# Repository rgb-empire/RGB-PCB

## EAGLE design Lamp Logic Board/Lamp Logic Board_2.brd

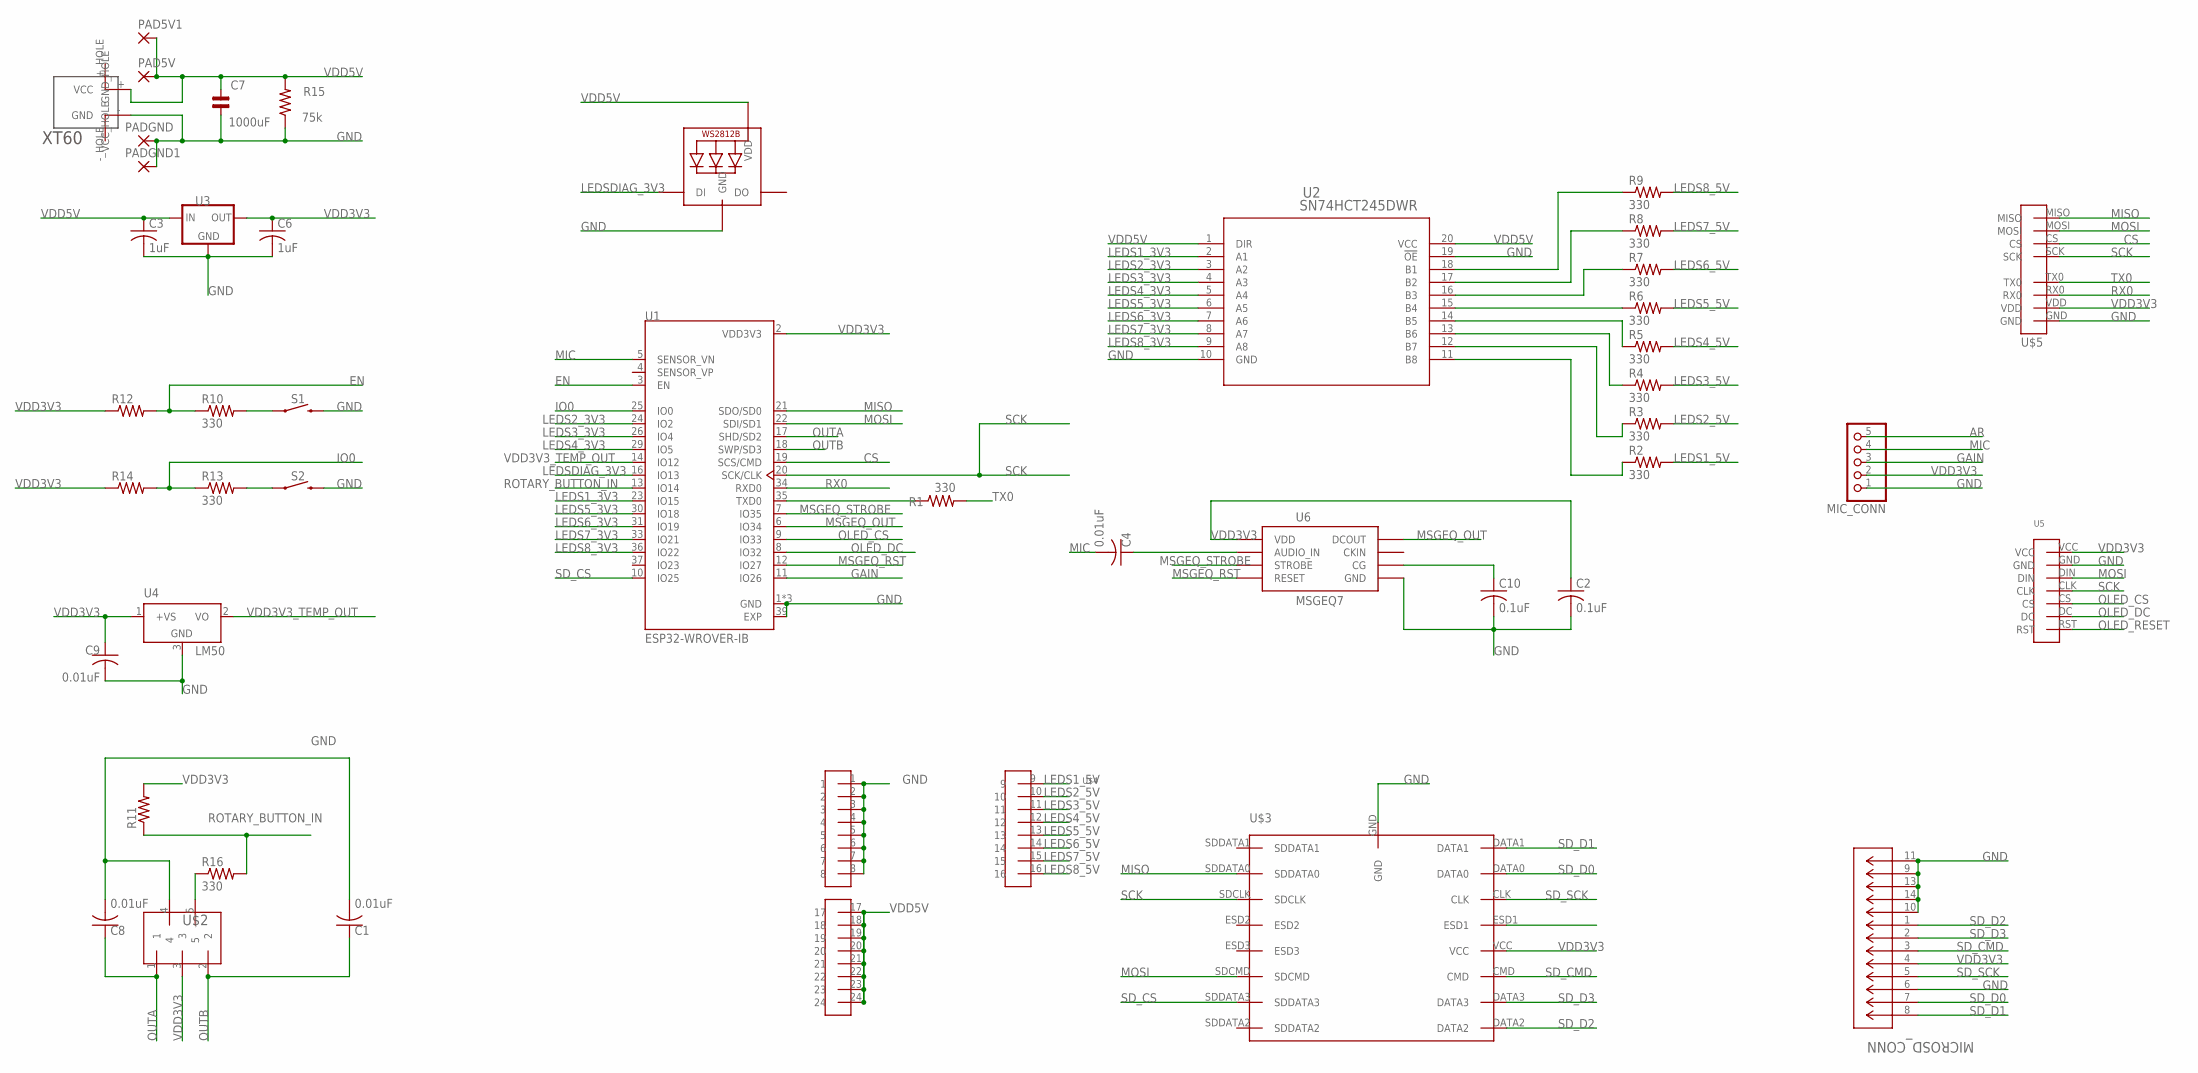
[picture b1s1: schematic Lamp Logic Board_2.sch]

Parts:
C1, C4, C8, C9: 0.01uF; C0402
C2, C10: 0.1uF; C0805
C3, C6: 1uF; C0402
C7: 1000uF; ENP2,0-5
LED1: WS2812B5050; WS2812B
MICROSD_CONN: LLC; CON00218_8
MIC_CONN: PINHD-1X5; 1X05
PAD5V, PAD5V1: SMD5; SMD2,54-5,08
PADGND, PADGND1: SMD5; SMD2,54-5,08
R1, R2, R3, R4, R5, R6, R7, R8, R9, R10, R13, R16: 330; R1206
R11, R12, R14: R-US_R0603; R0603
R15: 75k; 0309/12
S1, S2: MOMENTARY-SWITCH-SPST-SMD-6.0X3.5MM; TACTILE_SWITCH_SMD_6.0X3.5MM
U1: ESP32-WROVER-IB; XCVR_ESP32-WROVER-I
U2: SN74HCT245DWR; DW20
U3: LM1117MP-1.8; SOT223
U4: LM50; SOT23
U5: SPIOLED_STANDOFF; SPIOLED_STADOFF
U6: MSGEQ7DIL; DIL-08
U$1: XT60
U$2: EN11-HSM1AF15; EN11-HSM
U$3: CM1624-08DE
U$4: 3X8PINHEAD
U$5: 2X4PINHEAD

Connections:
AR: MIC_CONN.5
CS: U1.19 (SCS/CMD), U$5.CS
EN: R10.1, R12.2, U1.3 (EN)
GAIN: MIC_CONN.3, U1.11 (IO26)
GND: C1.2, C2.2, C3.2, C6.2, C7.1, C8.2, C9.2, C10.2, LED1.3-GND (GND), MICROSD_CONN.6, MICROSD_CONN.9, MICROSD_CONN.10, MICROSD_CONN.11, MICROSD_CONN.13, MICROSD_CONN.14, MIC_CONN.1, PADGND.1, PADGND1.1, R15.1, S1.2, S2.2, U1.1 (GND), U1.15 (GND), U1.38 (GND), U1.39 (EXP), U2.10 (GND), U2.19 (!OE), U3.1 (GND), U4.3 (GND), U5.GND, U6.2 (GND), U$1.- (GND), U$2.4, U$3.GND, U$4.1, U$4.2, U$4.3, U$4.4, U$4.5, U$4.6, U$4.7, U$4.8, U$5.GND
IO0: R13.1, R14.2, U1.25 (IO0)
LEDS1_3V3: U1.23 (IO15), U2.2 (A1)
LEDS1_5V: R2.2, U$4.9
LEDS2_3V3: U1.24 (IO2), U2.3 (A2)
LEDS2_5V: R3.2, U$4.10
LEDS3_3V3: U1.26 (IO4), U2.4 (A3)
LEDS3_5V: R4.2, U$4.11
LEDS4_3V3: U1.29 (IO5), U2.5 (A4)
LEDS4_5V: R5.2, U$4.12
LEDS5_3V3: U1.30 (IO18), U2.6 (A5)
LEDS5_5V: R6.2, U$4.13
LEDS6_3V3: U1.31 (IO19), U2.7 (A6)
LEDS6_5V: R7.2, U$4.14
LEDS7_3V3: U1.33 (IO21), U2.8 (A7)
LEDS7_5V: R8.2, U$4.15
LEDS8_3V3: U1.36 (IO22), U2.9 (A8)
LEDS8_5V: R9.2, U$4.16
LEDSDIAG_3V3: LED1.4-DIN (DI), U1.16 (IO13)
MIC: C4.2, MIC_CONN.4, U1.5 (SENSOR_VN)
MISO: U1.21 (SDO/SD0), U$3.SDDATA0, U$5.MISO
MOSI: U1.22 (SDI/SD1), U5.DIN, U$3.SDCMD, U$5.MOSI
MSGEQ_OUT: U1.6 (IO34), U6.3 (DCOUT)
MSGEQ_RST: U1.12 (IO27), U6.7 (RESET)
MSGEQ_STROBE: U1.7 (IO35), U6.4 (STROBE)
unnamed: R9.1, U2.18 (B1)
unnamed: R1.1, U1.35 (TXD0)
unnamed: C4.1, U6.5 (AUDIO_IN)
unnamed: C10.1, U6.6 (CG)
unnamed: R16.1, U$2.5
unnamed: R8.1, U2.17 (B2)
unnamed: R13.2, S2.1
unnamed: R10.2, S1.1
unnamed: R7.1, U2.16 (B3)
unnamed: R6.1, U2.15 (B4)
unnamed: R5.1, U2.14 (B5)
unnamed: R4.1, U2.13 (B6)
unnamed: R3.1, U2.12 (B7)
unnamed: R2.1, U2.11 (B8)
OLED_CS: U1.9 (IO33), U5.CS
OLED_DC: U1.8 (IO32), U5.DC
OLED_RESET: U5.RST
OUTA: C8.1, U1.17 (SHD/SD2), U$2.1
OUTB: C1.1, U1.18 (SWP/SD3), U$2.2
ROTARY_BUTTON_IN: R11.1, R16.2, U1.13 (IO14)
RX0: U1.34 (RXD0), U$5.RX0
SCK: U1.20 (SCK/CLK), U5.CLK, U$3.SDCLK, U$5.SCK
SD_CMD: MICROSD_CONN.3, U$3.CMD
SD_CS: U1.10 (IO25), U$3.SDDATA3
SD_D0: MICROSD_CONN.7, U$3.DATA0
SD_D1: MICROSD_CONN.8, U$3.DATA1
SD_D2: MICROSD_CONN.1, U$3.DATA2
SD_D3: MICROSD_CONN.2, U$3.DATA3
SD_SCK: MICROSD_CONN.5, U$3.CLK
TX0: R1.2, U$5.TX0
VDD3V3: C2.1, C6.1, C9.1, MICROSD_CONN.4, MIC_CONN.2, R11.2, R12.1, R14.1, U1.2 (VDD3V3), U3.2 (OUT), U3.4 (OUT), U4.1 (+VS), U5.VCC, U6.1 (VDD), U$2.3, U$3.VCC, U$5.VDD
VDD3V3_TEMP_OUT: U1.14 (IO12), U4.2 (VO)
VDD5V: C3.1, C7.2, LED1.1-VDD (VDD), PAD5V.1, PAD5V1.1, R15.2, U2.1 (DIR), U2.20 (VCC), U3.3 (IN), U$1.+ (VCC), U$4.17, U$4.18, U$4.19, U$4.20, U$4.21, U$4.22, U$4.23, U$4.24

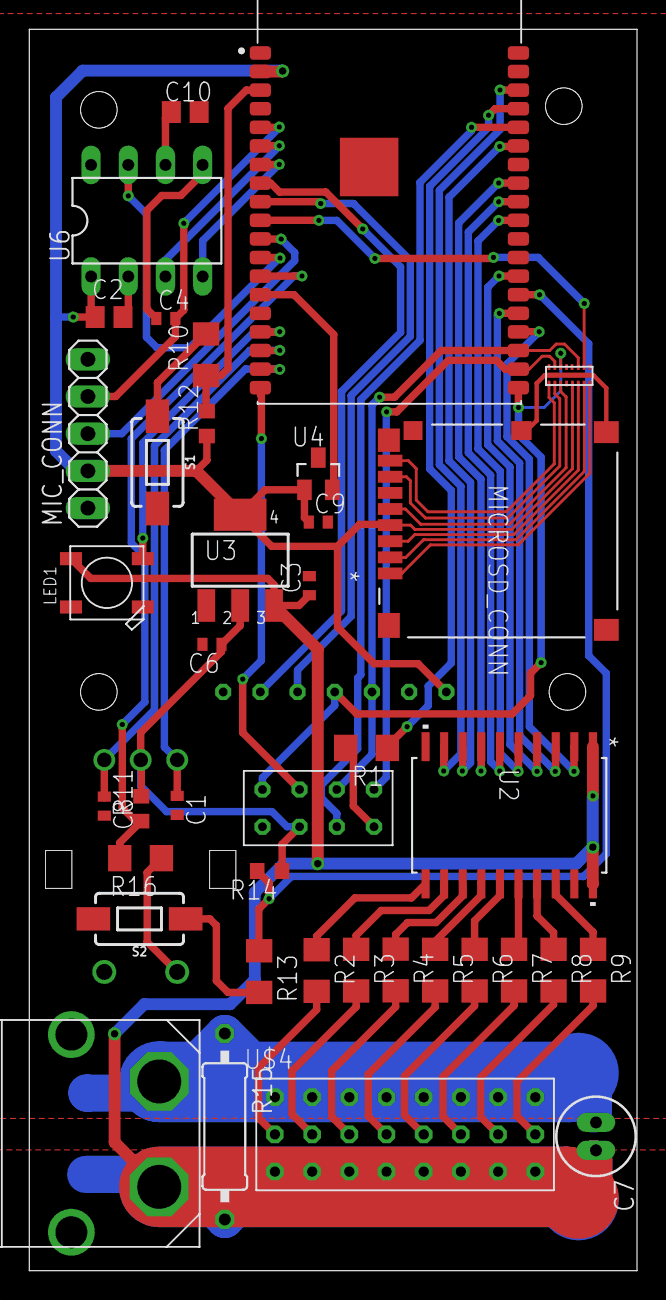
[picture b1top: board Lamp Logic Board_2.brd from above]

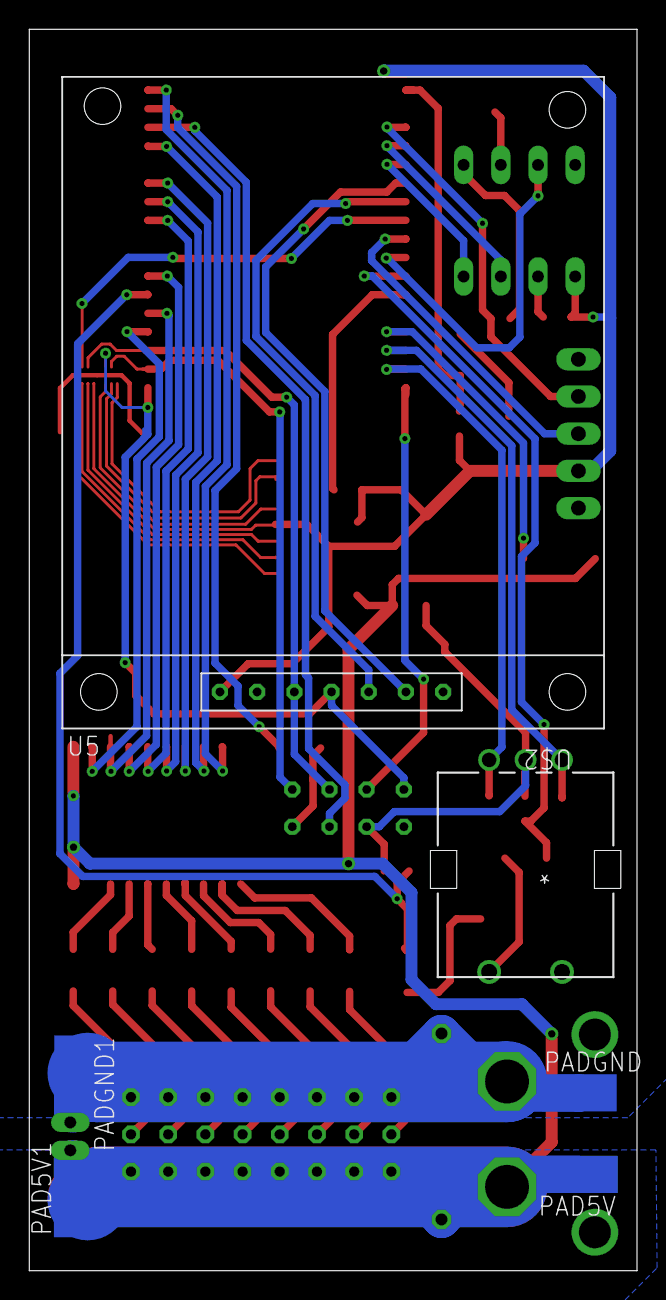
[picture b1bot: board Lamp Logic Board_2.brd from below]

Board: 2 copper layers, 41.5 x 84.8 mm, 45 parts (6 on the bottom side), 60 nets.

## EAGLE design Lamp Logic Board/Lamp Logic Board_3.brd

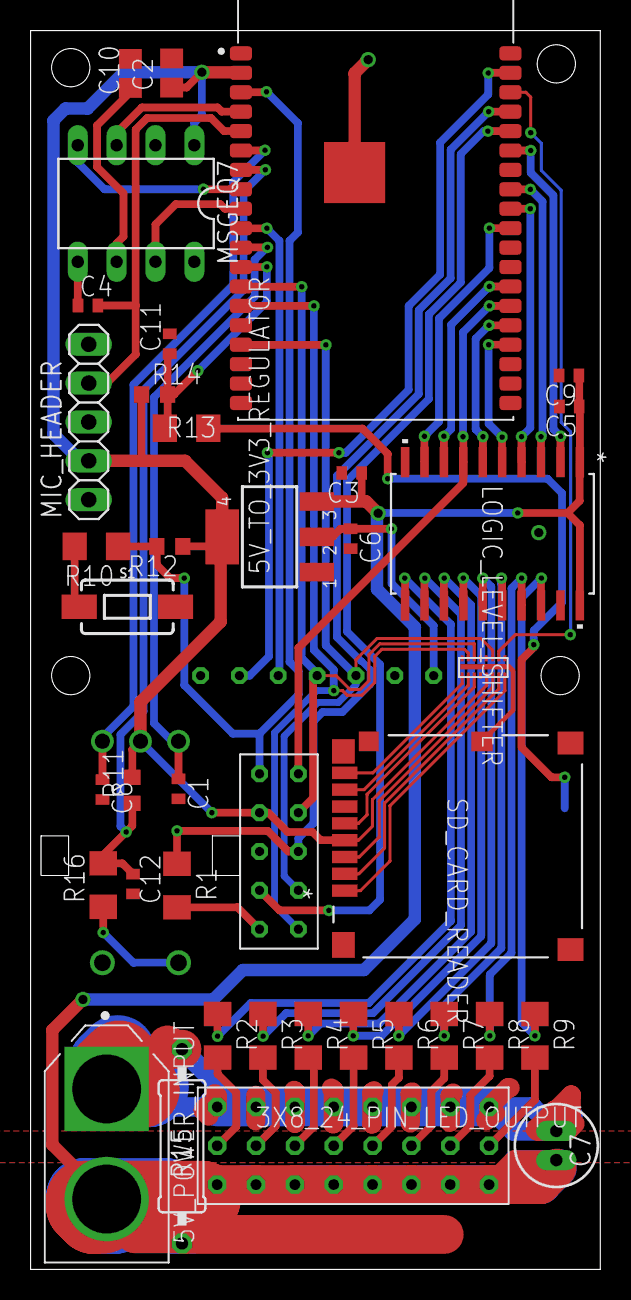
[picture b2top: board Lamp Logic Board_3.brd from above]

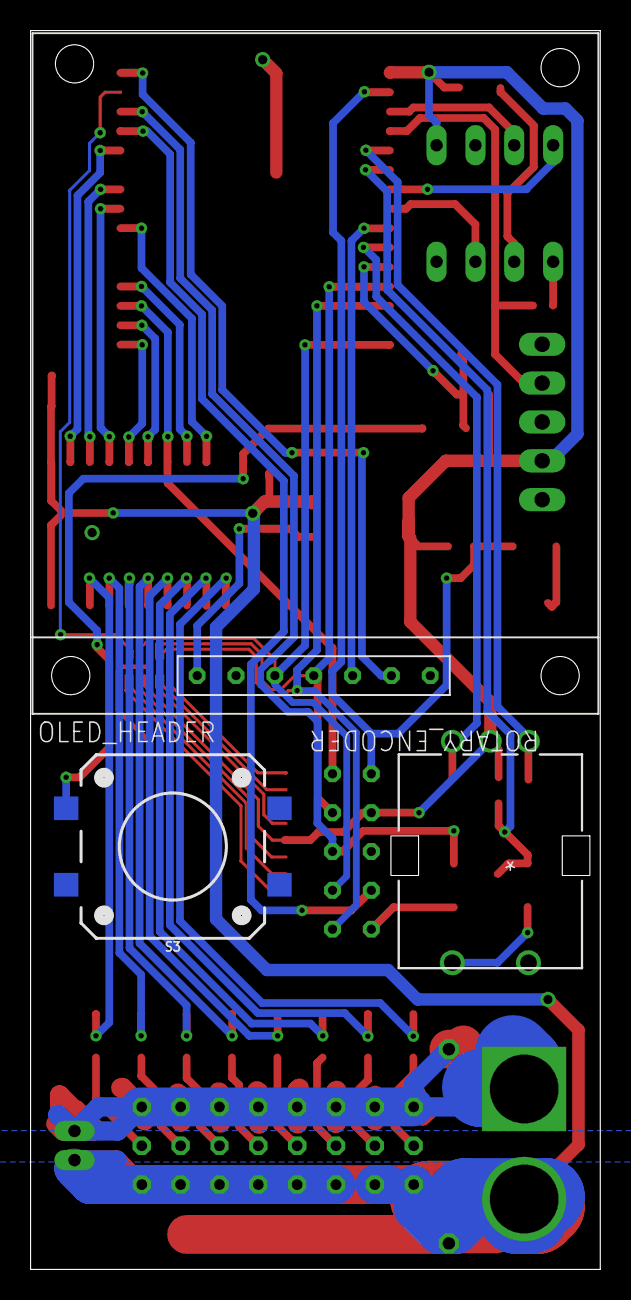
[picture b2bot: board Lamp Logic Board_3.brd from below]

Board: 2 copper layers, 37.2 x 81.0 mm, 42 parts (3 on the bottom side), 56 nets.

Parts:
3X8_24_PIN_LED_OUTPUT: 3X8PINHEAD
5V_POWER_INPUT: XT60-M; AMASS_XT60-M
5V_TO_3V3_REGULATOR: SOT223
C1, C4, C8: 0.01uF; C0402
C2, C10: 0.1uF; C0805
C3, C6, C9: 1uF; C0402
C5, C11, C12: 100nF; C0402
C7: 1000uF; ENP2,0-5
LOGIC_LEVEL_SHIFTER: SN74HCT245DWR; DW20
MIC_HEADER: 1X05
MSGEQ7: MSGEQ7DIL; DIL-08
OLED_HEADER: SPIOLED_STANDOFF; SPIOLED_STADOFF
R1, R2, R3, R4, R5, R6, R7, R8, R9, R10, R13, R16: 330; R1206
R11: R0603
R12, R14: 12k; R0603
R15: 75k; 0309/12
ROTARY_ENCODER: EN11-HSM1AF15; EN11-HSM
S1: TACTILE_SWITCH_SMD_6.0X3.5MM
S3: MOMENTARY-SWITCH-SPST-SMD-12MM; TACTILE_SWITCH_SMD_12MM
SD_CARD_FILTER: CM1624-08DE
SD_CARD_READER: LLC; CON00218_8
SERIAL/SPI_HEADER: 2X6PINHEAD
U1: ESP32-WROVER-IB; XCVR_ESP32-WROVER-I

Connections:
BEST_BUTTON: C11.1, R13.1, R14.2, U1.12
EN: R10.1, R12.2, SERIAL/SPI_HEADER.DTR, U1.3
GND: 3X8_24_PIN_LED_OUTPUT.1, 3X8_24_PIN_LED_OUTPUT.2, 3X8_24_PIN_LED_OUTPUT.3, 3X8_24_PIN_LED_OUTPUT.4, 3X8_24_PIN_LED_OUTPUT.5, 3X8_24_PIN_LED_OUTPUT.6, 3X8_24_PIN_LED_OUTPUT.7, 3X8_24_PIN_LED_OUTPUT.8, 5V_POWER_INPUT.1, 5V_TO_3V3_REGULATOR.1, C1.2, C2.2, C3.2, C5.2, C6.2, C7.1, C8.2, C9.2, C10.2, C11.2, C12.1, LOGIC_LEVEL_SHIFTER.10, LOGIC_LEVEL_SHIFTER.19, MIC_HEADER.1, MSGEQ7.2, OLED_HEADER.GND, R15.1, ROTARY_ENCODER.4, S1.2, S3.3, SD_CARD_FILTER.GND, SD_CARD_READER.6, SD_CARD_READER.9, SD_CARD_READER.10, SD_CARD_READER.11, SD_CARD_READER.13, SD_CARD_READER.14, SERIAL/SPI_HEADER.GND, U1.1, U1.15, U1.38, U1.39
HEADER_CS: R1.1, SERIAL/SPI_HEADER.CS, U1.35
LEDS1_3V3: LOGIC_LEVEL_SHIFTER.2, U1.33
LEDS1_5V: 3X8_24_PIN_LED_OUTPUT.9, R2.2
LEDS2_3V3: LOGIC_LEVEL_SHIFTER.3, U1.31
LEDS2_5V: 3X8_24_PIN_LED_OUTPUT.10, R3.2
LEDS3_3V3: LOGIC_LEVEL_SHIFTER.4, U1.30
LEDS3_5V: 3X8_24_PIN_LED_OUTPUT.11, R4.2
LEDS4_3V3: LOGIC_LEVEL_SHIFTER.5, U1.23
LEDS4_5V: 3X8_24_PIN_LED_OUTPUT.12, R5.2
LEDS5_3V3: LOGIC_LEVEL_SHIFTER.6, U1.24
LEDS5_5V: 3X8_24_PIN_LED_OUTPUT.13, R6.2
LEDS6_3V3: LOGIC_LEVEL_SHIFTER.7, SERIAL/SPI_HEADER.RTS, U1.25
LEDS6_5V: 3X8_24_PIN_LED_OUTPUT.14, R7.2
LEDS7_3V3: LOGIC_LEVEL_SHIFTER.8, U1.26
LEDS7_5V: 3X8_24_PIN_LED_OUTPUT.15, R8.2
LEDS8_3V3: LOGIC_LEVEL_SHIFTER.9, U1.29
LEDS8_5V: 3X8_24_PIN_LED_OUTPUT.16, R9.2
MIC: C4.2, MIC_HEADER.4, U1.5
MISO: SD_CARD_FILTER.SDDATA0, SERIAL/SPI_HEADER.MISO, U1.14
MOSI: OLED_HEADER.DIN, SD_CARD_FILTER.SDCMD, SERIAL/SPI_HEADER.MOSI, U1.16
MSGEQ_OUT: MSGEQ7.3, U1.4
MSGEQ_RST: MSGEQ7.7, U1.9
MSGEQ_STROBE: MSGEQ7.4, U1.8
unnamed: LOGIC_LEVEL_SHIFTER.18, R9.1
unnamed: C4.1, MSGEQ7.5
unnamed: C10.1, MSGEQ7.6
unnamed: R16.1, ROTARY_ENCODER.5
unnamed: LOGIC_LEVEL_SHIFTER.17, R8.1
unnamed: R13.2, S3.1
unnamed: R10.2, S1.1
unnamed: LOGIC_LEVEL_SHIFTER.16, R7.1
unnamed: LOGIC_LEVEL_SHIFTER.15, R6.1
unnamed: LOGIC_LEVEL_SHIFTER.14, R5.1
unnamed: LOGIC_LEVEL_SHIFTER.13, R4.1
unnamed: LOGIC_LEVEL_SHIFTER.12, R3.1
unnamed: LOGIC_LEVEL_SHIFTER.11, R2.1
OLED_CS: OLED_HEADER.CS, U1.10
OLED_DC: OLED_HEADER.DC, U1.37
ROTARY_BUTTON_OUT: C12.2, R11.1, R16.2, U1.7
ROTARY_OUT_A: C8.1, ROTARY_ENCODER.1, U1.6
ROTARY_OUT_B: C1.1, ROTARY_ENCODER.2, U1.11
RX0: SERIAL/SPI_HEADER.RX0, U1.34
SCK: OLED_HEADER.CLK, SD_CARD_FILTER.SDCLK, SERIAL/SPI_HEADER.SCK, U1.13
SD_CMD: SD_CARD_FILTER.CMD, SD_CARD_READER.3
SD_CS: SD_CARD_FILTER.SDDATA3, U1.36
SD_D0: SD_CARD_FILTER.DATA0, SD_CARD_READER.7
SD_D1: SD_CARD_FILTER.DATA1, SD_CARD_READER.8
SD_D2: SD_CARD_FILTER.DATA2, SD_CARD_READER.1
SD_D3: SD_CARD_FILTER.DATA3, SD_CARD_READER.2
SD_SCK: SD_CARD_FILTER.CLK, SD_CARD_READER.5
TX0: R1.2, SERIAL/SPI_HEADER.TX0
VDD3V3: 5V_TO_3V3_REGULATOR.2, 5V_TO_3V3_REGULATOR.4, C2.1, C6.1, MIC_HEADER.2, MSGEQ7.1, OLED_HEADER.VCC, R11.2, R12.1, R14.1, ROTARY_ENCODER.3, SD_CARD_FILTER.VCC, SD_CARD_READER.4, SERIAL/SPI_HEADER.VCC, U1.2
VDD5V: 3X8_24_PIN_LED_OUTPUT.17, 3X8_24_PIN_LED_OUTPUT.18, 3X8_24_PIN_LED_OUTPUT.19, 3X8_24_PIN_LED_OUTPUT.20, 3X8_24_PIN_LED_OUTPUT.21, 3X8_24_PIN_LED_OUTPUT.22, 3X8_24_PIN_LED_OUTPUT.23, 3X8_24_PIN_LED_OUTPUT.24, 5V_POWER_INPUT.2, 5V_TO_3V3_REGULATOR.3, C3.1, C5.1, C7.2, C9.1, LOGIC_LEVEL_SHIFTER.1, LOGIC_LEVEL_SHIFTER.20, R15.2

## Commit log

2019-08-20 Add files via upload
    Adding what I have for the PCB currently.
2019-08-21 Add files via upload
    First full schematic for the board, as well a components list.
2019-08-21 Add files via upload
    Added the SD Card Connector as well ESD Filter for it.
2019-08-21 Add files via upload
    Added connection for MSGEQ7 as well direct connections to MIC output.
2019-08-22 Add files via upload
    Uploading a version, that does not have a messed up board file.
2019-08-22 Add files via upload
    Adding the library folder used in the design. This includes more than the ones used in the design.
2019-08-22 updated board and stuff
2019-08-22 It's the £2 one.
2019-08-23 hahaha
2019-08-24 Another day closer to death...
2019-08-24 boom
2019-08-24 still getting stuck on file 99
2019-08-24 just schematic _3
2019-08-24 and the rest
2019-08-25 everything but those two pesky caps

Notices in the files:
parts and their libraries:
cap-pan40: Copyright (C) 2004, Bob Starr
SparkFun-Switches: Licensing: Creative Commons ShareAlike 4.0 International - https://creativecommons.org/licenses/by-sa/4.0
lm1117: (c) 2014 Samuel Lourenço
